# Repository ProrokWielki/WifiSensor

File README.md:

# WiFi Sensor

ESP-12F + bme280 sensor. It measures humidity, temperature and pressure. It communicates using mqtt. When in standby it consumes < 1mA which allows it to work for more then 6 months on one set of batteries.

### what you need
* ESP-12F - or compatible device
* BME280
* LT1129-3.3
* 2x 2xAA in series battery holders
* capacitors and resistors

###

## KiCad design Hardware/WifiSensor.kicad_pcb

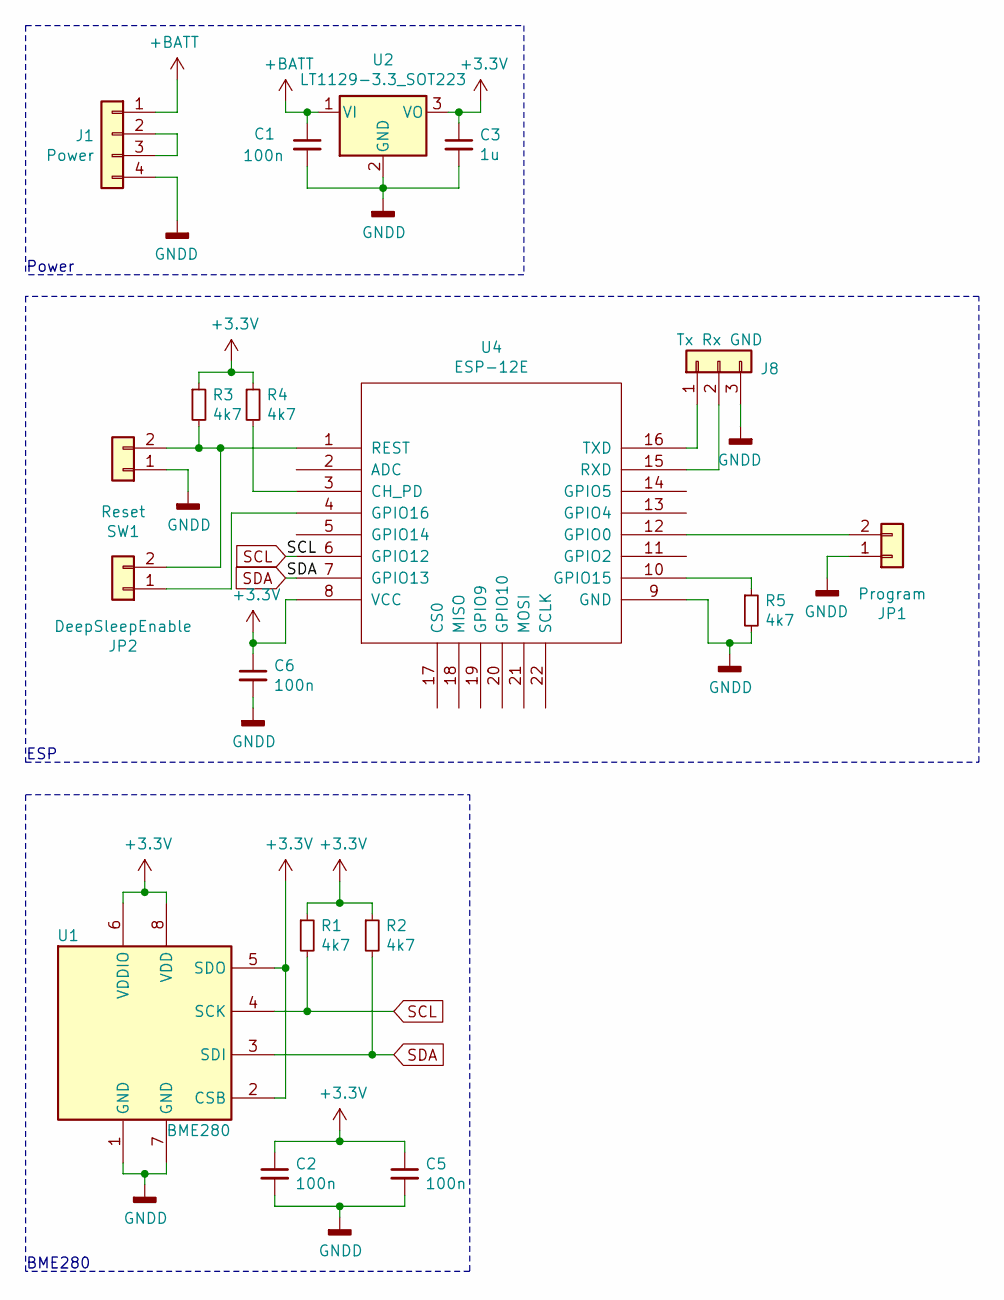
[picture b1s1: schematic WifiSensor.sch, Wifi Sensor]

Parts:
C1, C2, C5, C6: 100n; 0805
C3: 1u; 0805
J1: Power; Harwin_M20-89004xx_1x04_P2.54mm_Horizontal
J8: Tx Rx GND; Harwin_M20-89003xx_1x03_P2.54mm_Horizontal
JP1: Program; SolderJumper-2_P1.3mm_Open_RoundedPad1.0x1.5mm
JP2: DeepSleepEnable; SolderJumper-2_P1.3mm_Open_RoundedPad1.0x1.5mm
R1, R2, R3, R4, R5: 4k7; 0805
SW1: Reset; SolderJumper-2_P1.3mm_Open_RoundedPad1.0x1.5mm
U1: BME280; Bosch_LGA-8_2.5x2.5mm_P0.65mm_ClockwisePinNumbering
U2: LT1129-3.3_SOT223; SOT-223-3_TabPin2
U4: ESP-12E; ESP-12E_SMD

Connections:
+3V3: C2.1, C3.1, C5.1, C6.1, R1.1, R2.1, R3.1, R4.1, U1.2 (CSB), U1.5 (SDO), U1.6 (VDDIO), U1.8 (VDD), U2.3 (VO), U4.8 (VCC)
+BATT: C1.1, J1.1, U2.1 (VI)
GNDD: C1.2, C2.2, C3.2, C5.2, C6.2, J1.4, J8.3, JP1.1, R5.2, SW1.1, U1.1 (GND), U1.7 (GND), U2.2 (GND), U4.9 (GND)
unnamed: J1.2, J1.3
unnamed: J8.1, U4.16 (TXD)
unnamed: J8.2, U4.15 (RXD)
unnamed: JP1.2, U4.12 (GPIO0)
unnamed: JP2.1, U4.4 (GPIO16)
unnamed: JP2.2, R3.2, SW1.2, U4.1 (REST)
unnamed: R4.2, U4.3 (CH_PD)
unnamed: R5.1, U4.10 (GPIO15)
SCL: R1.2, U1.4 (SCK), U4.6 (GPIO12)
SDA: R2.2, U1.3 (SDI), U4.7 (GPIO13)

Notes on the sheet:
BME280
Power
ESP

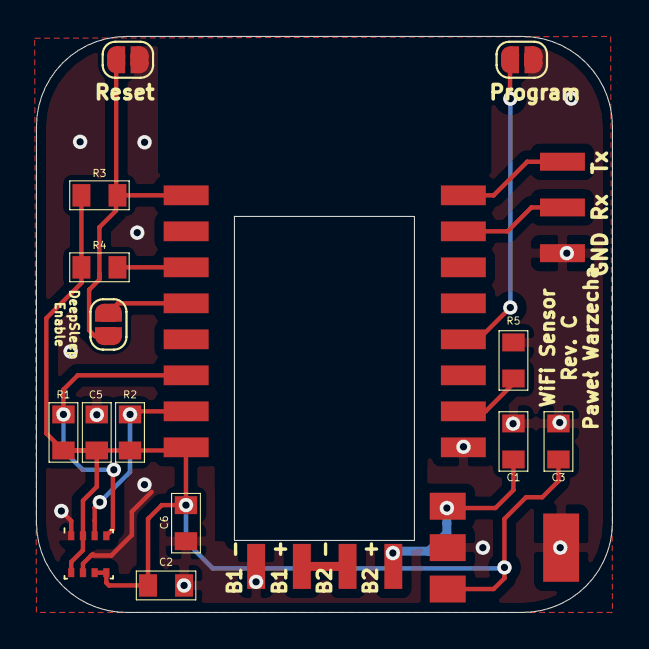
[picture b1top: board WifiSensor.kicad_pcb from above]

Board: 2 copper layers, 32.0 x 32.0 mm, 18 parts (0 on the bottom side), 13 nets.

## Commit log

2022-08-02 Hardware Rev. A
2022-08-03 Rev. B
2022-08-03 Added changelog
2022-08-14 Revision C
2022-08-15 initial software
2022-08-25 single read from bme, bme in normal mode
2023-05-01 New version of esp_mqtt_helpers.
2023-05-01 Added longer wait for wifi connection.
2024-04-09 Make WifiSensor more power efficient
    * More frequent wifi status polling
    * bme in force mode
    * shorter delay after publish
    * wifi persitent disabled
2024-04-11 Added .gitignore file
2024-04-13 Added Readme
